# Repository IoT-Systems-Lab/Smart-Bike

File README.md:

# Smart Bike Project group A

This repository contains the work for our **Smart Bike** project, part of the university IoT lab.  
The goal is to design a lightweight, low-power system that collects and transmits sensor data from a bicycle in real time — the first step toward a fully autonomous bike.

---

## Project Overview

The Smart Bike is equipped with several sensors to monitor movement, position, and environment data.  
All information is sent wirelessly to a gateway, which forwards it to a dashboard for live visualization.

We aim to:
- Collect data from multiple onboard sensors (speed, IMU, GPS, environment, …)
- Transmit it using **BLE 5 Long Range** to a **low-power gateway**
- Forward the processed data to a **dashboard** via **Wi-Fi**
- Keep everything lightweight, efficient, and modular

---

## System Architecture

**1. Bike (Sensor Node)**  
- Equipped with sensors for motion, speed, and environment  
- Communicates via **Bluetooth Low Energy (BLE 5 LR)**  

**2. Gateway**  
- Based on **ESP32-C3** microcontroller  
- Receives BLE data and sends it to the dashboard over Wi-Fi  
- Optimized for low power and simple integration  

**3. Dashboard**  
- Displays live bike data  
- Can be web-based or desktop-based  

---

## Group A Members

| Name               | Team                 | Role                   |
|--------------------|----------------------|------------------------|
| Beau Forrez        | Gateway & Dashboard  |                        |
| Elias Neels        | Gateway & Dashboard  |                        |
| Kjell Naessens     | Gateway & Dashboard  | Team Leader            |
| Wout Batselé       | Gateway & Dashboard  |                        |
| Charlotte Bert     | Sensors              | Time manager           |
| Niels Verhoeve     | Sensors              | Communication manager  |
| Arne Van der Stede | Sensors              |                        |
| Syme Vandenbosch   | Sensors              | Buget manager          |
| Daan Vercammen     | Sensors              | Team Leader            |

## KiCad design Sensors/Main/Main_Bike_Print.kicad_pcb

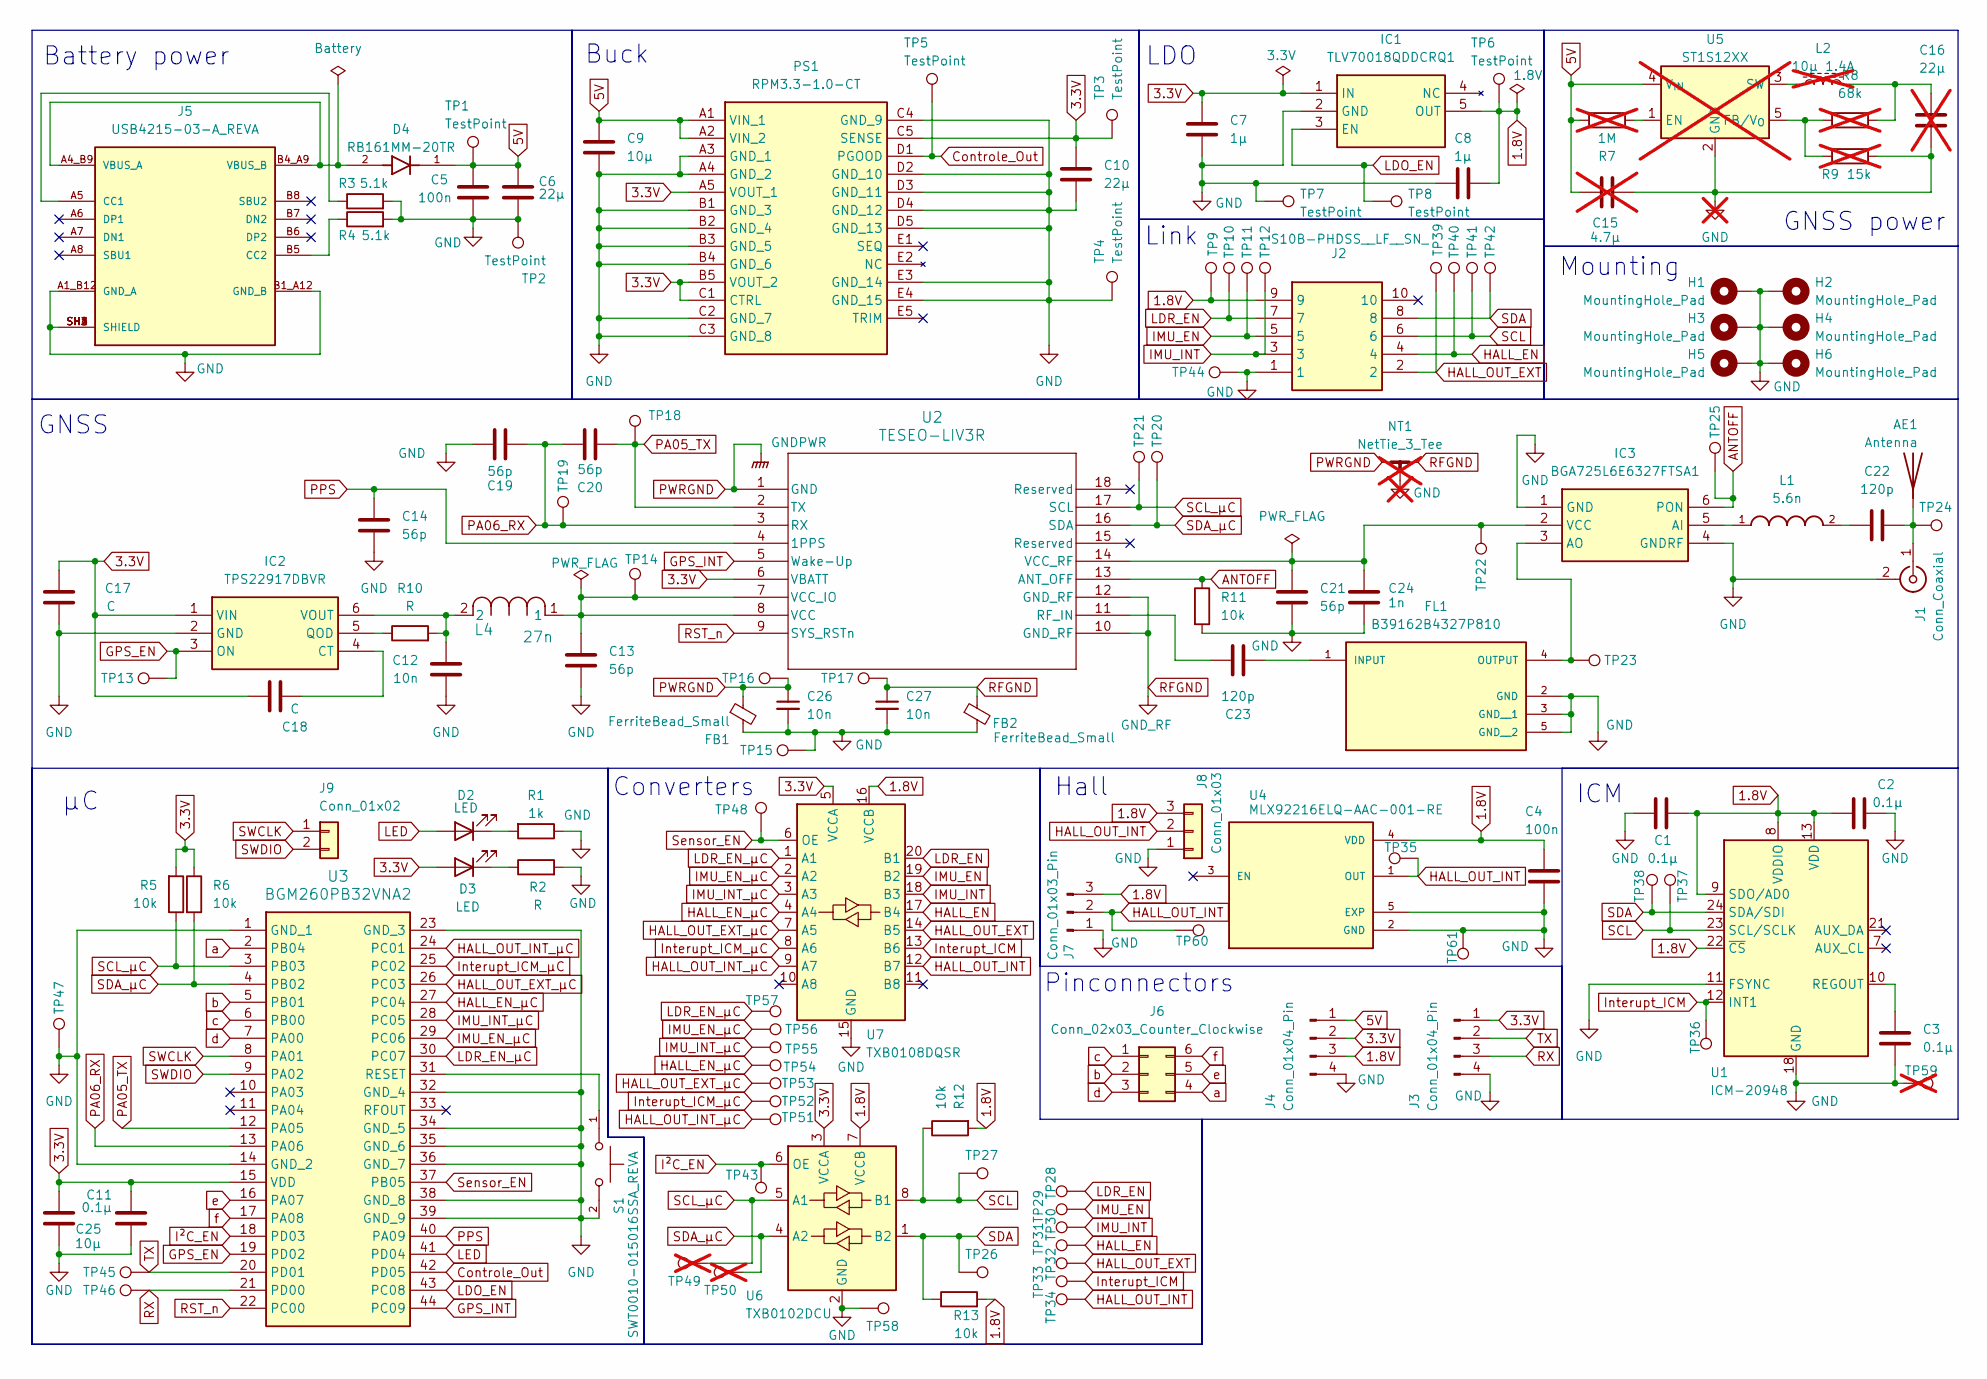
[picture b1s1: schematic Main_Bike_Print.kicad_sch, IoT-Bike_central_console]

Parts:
AE1: Antenna
C1, C2, C3, C11: 0.1µ; C_0603_1608Metric_Pad1.08x0.95mm_HandSolder
C4, C5: 100n; C_0603_1608Metric_Pad1.08x0.95mm_HandSolder
C6, C10: 22µ; C_0603_1608Metric_Pad1.08x0.95mm_HandSolder
C7, C8: 1µ; C_0603_1608Metric_Pad1.08x0.95mm_HandSolder
C9, C25: 10µ; C_0603_1608Metric_Pad1.08x0.95mm_HandSolder
C12, C26, C27: 10n; C_0603_1608Metric_Pad1.08x0.95mm_HandSolder
C13, C14, C19, C20, C21: 56p; C_0603_1608Metric_Pad1.08x0.95mm_HandSolder
C15: 4.7µ; not fitted
C16: 22µ; not fitted
C17, C18: C; C_0603_1608Metric_Pad1.08x0.95mm_HandSolder
C22, C23: 120p; C_0603_1608Metric_Pad1.08x0.95mm_HandSolder
C24: 1n; C_0603_1608Metric_Pad1.08x0.95mm_HandSolder
D2, D3: LED; LED_0603_1608Metric_Pad1.05x0.95mm_HandSolder
D4: RB161MM-20TR; RB161MM20TR
FB1, FB2: FerriteBead_Small; L_0603_1608Metric_Pad1.05x0.95mm_HandSolder
FL1: B39162B4327P810; FIL_B39162B4327P810; PARTREV October 25, 2019
H1, H2, H3, H4, H5, H6: MountingHole_Pad; MountingHole_3.2mm_M3_Pad_Via
IC1: TLV70018QDDCRQ1; SOT95P280X110-5N; Mouser Part Number 595-TLV70018QDDCRQ1
IC2: TPS22917DBVR; SOT95P280X145-6N; Mouser Part Number 595-TPS22917DBVR
IC3: BGA725L6E6327FTSA1; BGS12SN6E6327XTSA1; Manufacturer_Part_Number BGA725L6E6327FTSA1
J1: Conn_Coaxial; U.FL_Hirose_U.FL-R-SMT-1_Vertical
J2: S10B-PHDSS__LF__SN_; S10BPHDSSLFSN; Manufacturer_Part_Number S10B-PHDSS (LF)(SN)
J3, J4: Conn_01x04_Pin; PinSocket_1x04_P2.54mm_Vertical
J5: USB4215-03-A_REVA; GCT_USB4215-03-A_REVA; PARTREV A
J6: Conn_02x03_Counter_Clockwise; PinHeader_2x03_P2.54mm_Vertical
J7: Conn_01x03_Pin; PinSocket_1x03_P2.54mm_Vertical
J8: Conn_01x03; JST_PH_S3B-PH-K_1x03_P2.00mm_Horizontal
J9: Conn_01x02; PinSocket_1x02_P2.54mm_Vertical
L1: 5.6n; IND_0402CS-5N6XJRW; PARTREV 08/06/21
L2: 10µ 1.4A; not fitted
L4: 27n; IND_LQG15HNR10J02_MUR
NT1: NetTie_3_Tee; NetTie-3_SMD_Pad2.0mm; not fitted
PS1: RPM3.3-1.0-CT; RPM3310CT; Manufacturer_Part_Number RPM3.3-1.0-CT
R1: 1k; R_0603_1608Metric_Pad0.98x0.95mm_HandSolder
R2, R10: R; R_0603_1608Metric_Pad0.98x0.95mm_HandSolder
R3, R4: 5.1k; R_0603_1608Metric_Pad0.98x0.95mm_HandSolder
R5, R6, R11, R12, R13: 10k; R_0603_1608Metric_Pad0.98x0.95mm_HandSolder
R7: 1M; not fitted
R8: 68k; not fitted
R9: 15k; not fitted
S1: SWT0010-015016SSA_REVA; SW_SWT0010-015016SSA_REVA; PARTREV A
TP1, TP2, TP3, TP4, TP5, TP6, TP7, TP8, TP9, TP10, TP11, TP12, TP13, TP14, TP15, TP16, TP17, TP18, TP19, TP20, TP21, TP22, TP23, TP24, TP25, TP26, TP27, TP28, TP29, TP30, TP31, TP32, TP33, TP34, TP35, TP36, TP37, TP38, TP39, TP40, TP41, TP42, TP43, TP44, TP45, TP46, TP47, TP48, TP51, TP52, TP53, TP54, TP55, TP56, TP57, TP58, TP60, TP61: TestPoint; TestPoint_Pad_D1.0mm
TP49, TP50, TP59: TestPoint; TestPoint_Pad_D1.0mm; not fitted
U1: ICM-20948; InvenSense_QFN-24_3x3mm_P0.4mm
U2: TESEO-LIV3R; ARRAY_LIV3R_STM
U3: BGM260PB32VNA2; Manufacturer_Part_Number BGM260PB32VNA2
U4: MLX92216ELQ-AAC-001-RE; SON65P120X160X40-5N; PARTREV 1.0
U5: ST1S12XX; TSOT-23-5; not fitted
U6: TXB0102DCU; VSSOP-8_2.3x2mm_P0.5mm
U7: TXB0108DQSR; USON-20_2x4mm_P0.4mm

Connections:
1.8V: C1.2, C2.1, C4.1, C8.1, IC1.5 (OUT), J2.9, J4.3, J7.3, J8.3, R12.2, R13.2, TP6.1, TP9.1, U1.8 (VDDIO), U1.9 (SDO/AD0), U1.13 (VDD), U1.22 (~CS), U4.4 (VDD), U6.7 (VCCB), U7.16 (VCCB)
3.3V: C7.1, C10.1, C11.2, C17.1, C18.1, C25.2, D3.2 (A), IC1.1 (IN), IC2.1 (VIN), J3.1, J4.2, PS1.A5 (VOUT_1), PS1.B5 (VOUT_2), PS1.C1 (CTRL), PS1.C5 (SENSE), R5.2, R6.1, TP3.1, U2.6 (VBATT), U3.15 (VDD), U6.3 (VCCA), U7.5 (VCCA)
5V: C5.1, C6.1, C9.1, C15.1, D4.1, J4.1, PS1.A1 (VIN_1), PS1.A2 (VIN_2), R7.1, TP1.1, U5.4 (V_{IN})
ANTOFF: IC3.6 (PON), R11.1, TP25.1, U2.13 (ANT_OFF)
Controle_Out: PS1.D1 (PGOOD), TP5.1, U3.42 (PD05)
GND: C1.1, C2.2, C3.2, C4.2, C5.2, C6.2, C7.2, C8.2, C9.2, C10.2, C11.1, C12.2, C13.2, C14.2, C15.2, C16.2, C17.2, C19.2, C21.2, C24.2, C25.1, C26.2, C27.2, FB1.2, FB2.2, FL1.2 (GND), FL1.3 (GND__1), FL1.5 (GND__2), H1.1, H2.1, H3.1, H4.1, H5.1, H6.1, IC1.2 (GND), IC2.2 (GND), IC3.1 (GND), IC3.4 (GNDRF), J1.2 (Ext), J2.1, J3.4, J4.4, J5.A1_B12 (GND_A), J5.B1_A12 (GND_B), J5.SH1 (SHIELD), J5.SH2 (SHIELD), J5.SH3 (SHIELD), J5.SH4 (SHIELD), J7.1, J8.1, NT1.3, PS1.A3 (GND_1), PS1.A4 (GND_2), PS1.B1 (GND_3), PS1.B2 (GND_4), PS1.B3 (GND_5), PS1.B4 (GND_6), PS1.C2 (GND_7), PS1.C3 (GND_8), PS1.C4 (GND_9), PS1.D2 (GND_10), PS1.D3 (GND_11), PS1.D4 (GND_12), PS1.D5 (GND_13), PS1.E3 (GND_14), PS1.E4 (GND_15), R1.1, R2.2, R3.2, R4.2, R9.2, R11.2, S1.2, TP2.1, TP4.1, TP7.1, TP15.1, TP44.1, TP47.1, TP58.1, TP59.1, TP61.1, U1.11 (FSYNC), U1.18 (GND), U1.20 (GND), U3.1 (GND_1), U3.14 (GND_2), U3.23 (GND_3), U3.32 (GND_4), U3.34 (GND_5), U3.35 (GND_6), U3.36 (GND_7), U3.38 (GND_8), U3.39 (GND_9), U4.2 (GND), U4.5 (EXP), U5.2 (GND), U6.2 (GND), U7.15 (GND)
GPS_EN: IC2.3 (ON), TP13.1, U3.19 (PD02)
GPS_INT: U2.5 (Wake-Up), U3.44 (PC09)
HALL_EN: J2.4, TP31.1, TP40.1, U7.17 (B4)
HALL_EN_µC: TP54.1, U3.27 (PC04), U7.4 (A4)
HALL_OUT_EXT: J2.2, TP32.1, TP39.1, U7.14 (B5)
HALL_OUT_EXT_µC: TP53.1, U3.26 (PC03), U7.7 (A5)
HALL_OUT_INT: J7.2, J8.2, TP34.1, TP35.1, TP60.1, U4.1 (OUT), U7.12 (B7)
HALL_OUT_INT_µC: TP51.1, U3.24 (PC01), U7.9 (A7)
IMU_EN: J2.5, TP11.1, TP29.1, U7.19 (B2)
IMU_EN_µC: TP56.1, U3.29 (PC06), U7.2 (A2)
IMU_INT: J2.3, TP12.1, TP30.1, U7.18 (B3)
IMU_INT_µC: TP55.1, U3.28 (PC05), U7.3 (A3)
Interupt_ICM: TP33.1, TP36.1, U1.12 (INT1), U7.13 (B6)
Interupt_ICM_µC: TP52.1, U3.25 (PC02), U7.8 (A6)
I²C_EN: TP43.1, U3.18 (PD03), U6.6 (OE)
LDO_EN: IC1.3 (EN), TP8.1, U3.43 (PC08)
LDR_EN: J2.7, TP10.1, TP28.1, U7.20 (B1)
LDR_EN_µC: TP57.1, U3.30 (PC07), U7.1 (A1)
LED: D2.2 (A), U3.41 (PD04)
unnamed: AE1.1, C22.1, J1.1 (In), TP24.1
unnamed: C16.1, L2.2, R8.1
unnamed: C22.2, L1.2
unnamed: D2.1 (K), R1.2
unnamed: D3.1 (K), R2.1
unnamed: C23.1, FL1.1 (INPUT)
unnamed: FL1.4 (OUTPUT), IC3.3 (AO), TP23.1
unnamed: C18.2, IC2.4 (CT)
unnamed: IC2.5 (QOD), R10.1
unnamed: C12.1, IC2.6 (VOUT), L4.2, R10.2
unnamed: IC3.5 (AI), L1.1
unnamed: C21.1, C24.1, IC3.2 (VCC), TP22.1, U2.14 (VCC_RF)
unnamed: J5.A5 (CC1), R3.1
unnamed: J5.B5 (CC2), R4.1
unnamed: D4.2, J5.A4_B9 (VBUS_A), J5.B4_A9 (VBUS_B)
unnamed: L2.1, U5.3 (SW)
unnamed: R7.2, U5.1 (EN)
unnamed: R8.2, R9.1, U5.5 (FB/V_{O})
unnamed: C3.1, U1.10 (REGOUT)
unnamed: C23.2, U2.11 (RF_IN)
unnamed: C13.1, L4.1, TP14.1, U2.7 (VCC_IO), U2.8 (VCC)
unnamed: S1.1, U3.31 (RESET)
PA05_TX: C20.1, TP18.1, U2.2 (TX), U3.12 (PA05)
PA06_RX: C19.1, C20.2, TP19.1, U2.3 (RX), U3.13 (PA06)
PPS: C14.1, U2.4 (1PPS), U3.40 (PA09)
PWRGND: C26.1, FB1.1, NT1.1, TP16.1, U2.1 (GND)
RFGND: C27.1, FB2.1, NT1.2, TP17.1, U2.10 (GND_RF), U2.12 (GND_RF)
RST_n: U2.9 (SYS_RSTn), U3.22 (PC00)
RX: J3.3, TP46.1, U3.21 (PD00)
SCL: J2.6, R12.1, TP27.1, TP37.1, TP41.1, U1.23 (SCL/SCLK), U6.8 (B1)
SCL_µC: R5.1, TP21.1, TP49.1, U2.17 (SCL), U3.3 (PB03), U6.5 (A1)
SDA: J2.8, R13.1, TP26.1, TP38.1, TP42.1, U1.24 (SDA/SDI), U6.1 (B2)
SDA_µC: R6.2, TP20.1, TP50.1, U2.16 (SDA), U3.4 (PB02), U6.4 (A2)
SWCLK: J9.1, U3.8 (PA01)
SWDIO: J9.2, U3.9 (PA02)
Sensor_EN: TP48.1, U3.37 (PB05), U7.6 (OE)
TX: J3.2, TP45.1, U3.20 (PD01)
a: J6.4, U3.2 (PB04)
b: J6.2, U3.5 (PB01)
c: J6.1, U3.6 (PB00)
d: J6.3, U3.7 (PA00)
e: J6.5, U3.16 (PA07)
f: J6.6, U3.17 (PA08)

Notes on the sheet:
Battery power
Link
Converters
ICM
LDO
Mounting
Pinconnectors
GNSS
Buck
GNSS power
Hall

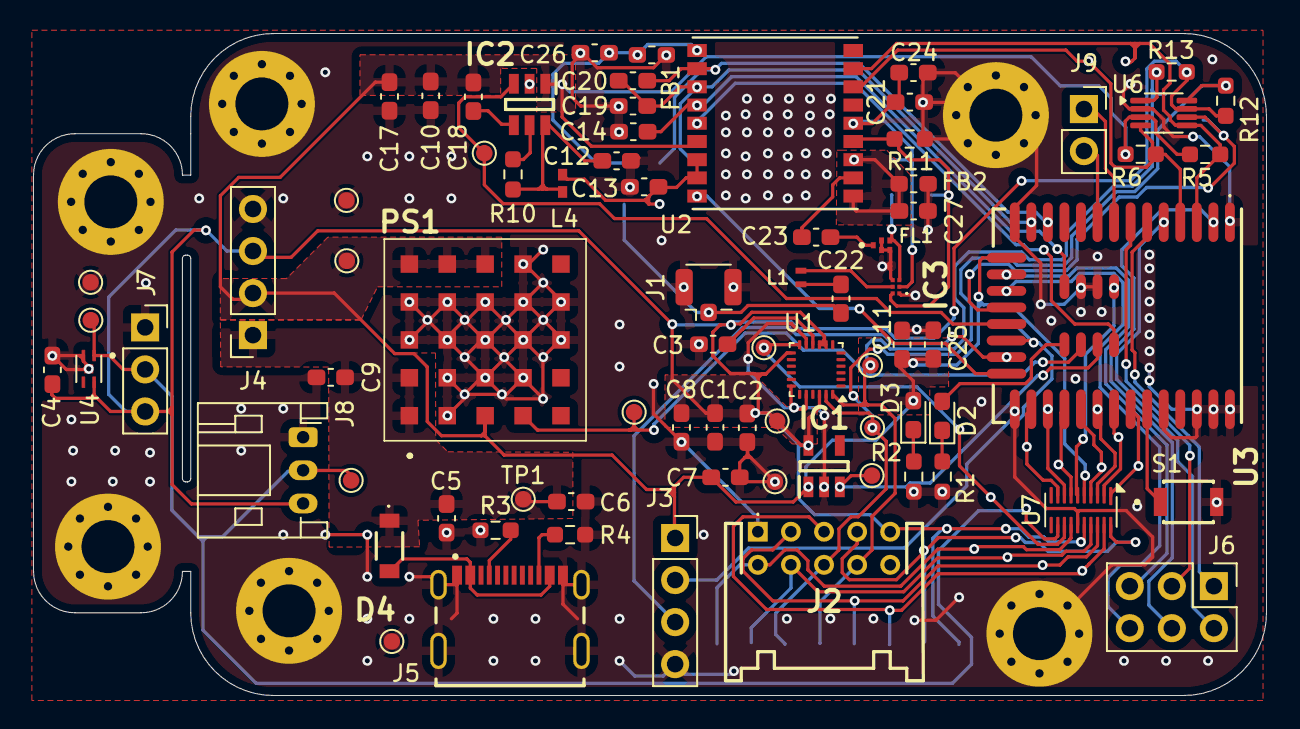
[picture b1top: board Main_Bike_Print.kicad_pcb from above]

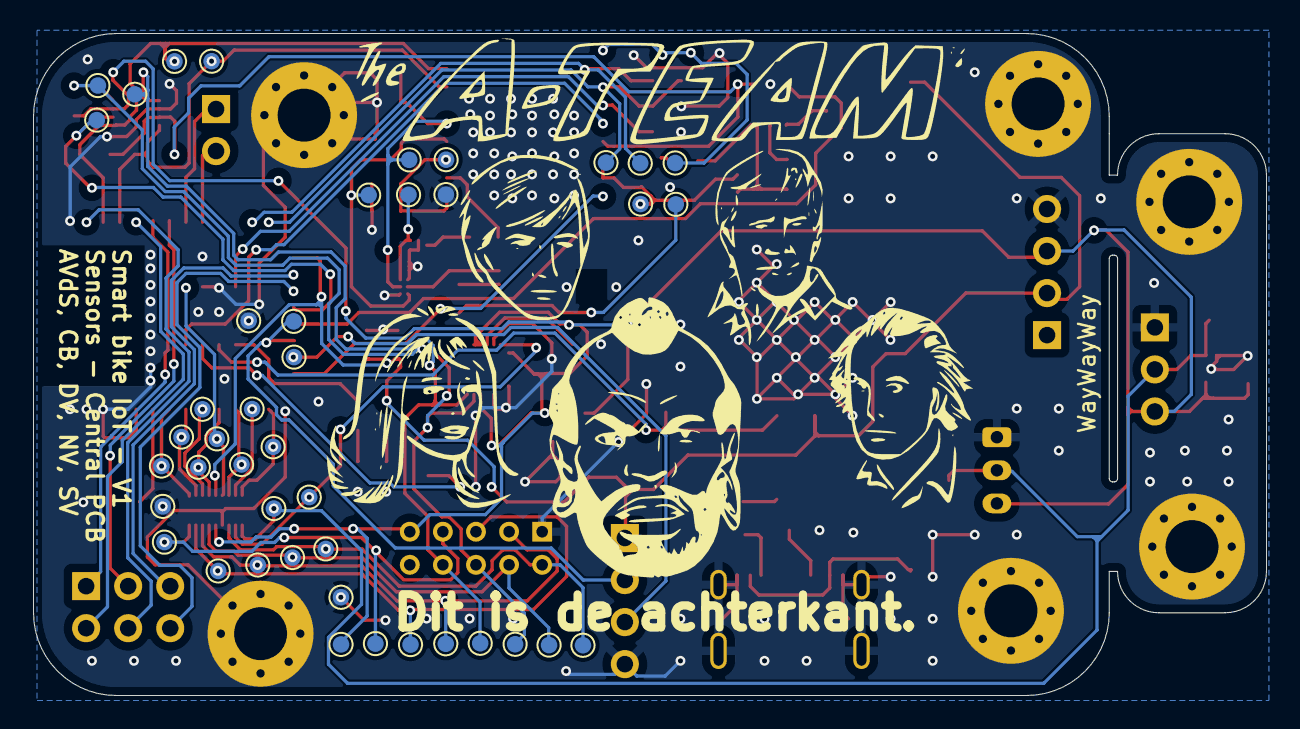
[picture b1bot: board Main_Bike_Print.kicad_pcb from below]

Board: 2 copper layers, 74.5 x 40.0 mm, 127 parts (43 on the bottom side), 64 nets.

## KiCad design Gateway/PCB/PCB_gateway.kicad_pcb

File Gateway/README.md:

# Gateway for Smart Bike Monitoring System

The purpose of the gateway is to receive data from a smart bike over BLE long range and write it to an InfluxDB database over a WiFi connection.
The dashboard is visualized using Grafana. This accesses the InfluxDB database using its HTTP API.

Both the database and the dashboard are hosted in the cloud using free-tier services. The database is hosted on InfluxDB Cloud and the Grafana dashboard is hosted on Grafana Cloud.

It is also possible to host both the database and the dashboard locally using Docker containers. These could be hosted on a personal server. Instructions for these containers are provided in the /Server folder.

## System overview

```
   Smart Bike
         | (BLE long range)
         v
      Gateway
         | (HTTP API)
         v
   InfluxDB Cloud
         | (HTTP API)
         v
   Grafana Cloud
```

## Code for the Gateway

The code for the gateway is written in c++ using the Arduino framework. It is designed to run on an ESP32 microcontroller with both WiFi and BLE long range capabilities.

## Link to dashboard and database

- Gateway WiFi repeater: https://github.com/martin-ger/esp32_nat_router/tree/master
- InfluxDB Cloud: https://cloud2.influxdata.com/
- Grafana Cloud: https://grafana.com/cloud
- Grafana Dashboard: https://boombike.grafana.net/public-dashboards/a31db9c51b8144fbb526a16ae5137e5a?fbclid=IwY2xjawNm6t9leHRuA2FlbQIxMQABHihIpa4uVn0q4TQ20HxuqrC6knFB-QV5GCWbPZI-nRs55s2GTs8DI9WtZkRM_aem_m_eqAt-B783CyasroQSzHg

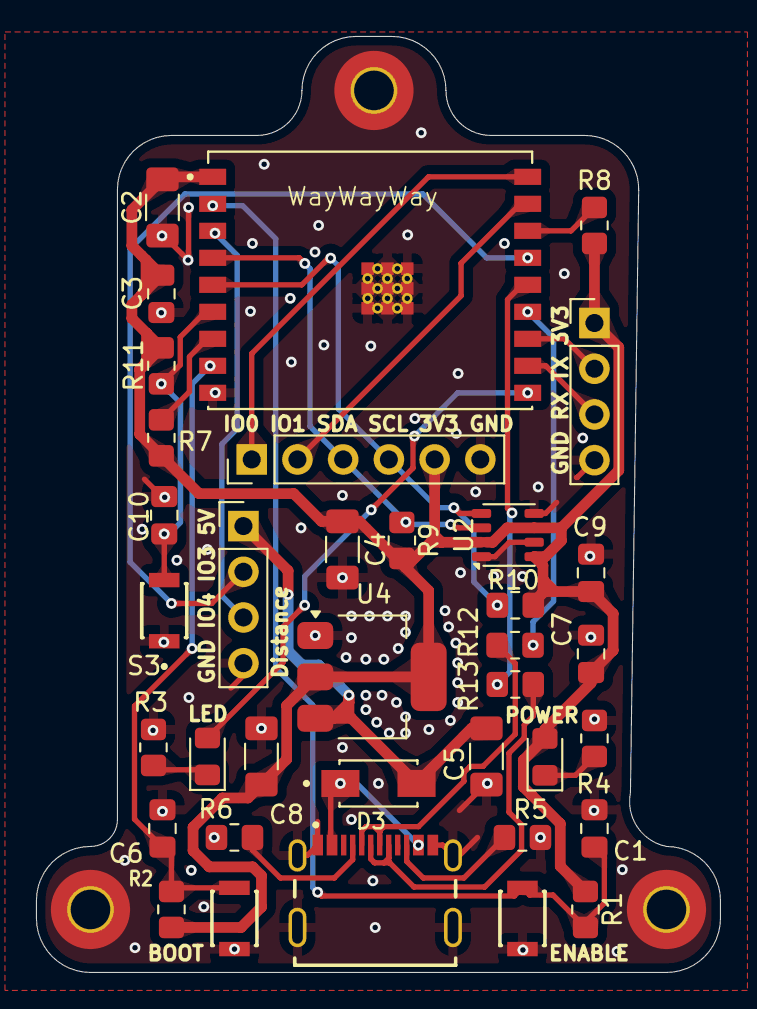
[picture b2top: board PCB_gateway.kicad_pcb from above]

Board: 2 copper layers, 38.0 x 52.0 mm, 39 parts (0 on the bottom side), 26 nets.

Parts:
BOOT: SWT0010-015016SSA_REVA; SW_SWT0010-015016SSA_REVA
C1, C3, C6, C10: 0.1u; C_0805_2012Metric_Pad1.18x1.45mm_HandSolder
C2, C4, C5, C8: 10u; C_1206_3216Metric_Pad1.33x1.80mm_HandSolder
C7, C9: 100n; C_0805_2012Metric_Pad1.18x1.45mm_HandSolder
D3: D_Schottky; DIOM4325X250N
EN: SWT0010-015016SSA_REVA; SW_SWT0010-015016SSA_REVA
H1, H2, H3: MountingHole_Pad; MountingHole_2.2mm_M2_Pad_TopBottom
J1: USB4215-03-A_REVA; GCT_USB4215-03-A_REVA
J2: Conn_01x06_Pin; PinHeader_1x06_P2.54mm_Vertical
J3, J4: Conn_01x04_Pin; PinHeader_1x04_P2.54mm_Vertical
LED: LED; LED_0805_2012Metric_Pad1.15x1.40mm_HandSolder
POWER: LED; LED_0805_2012Metric_Pad1.15x1.40mm_HandSolder
R1, R2, R7, R8, R11: 10k; R_0805_2012Metric_Pad1.20x1.40mm_HandSolder
R3, R4: 1k; R_0805_2012Metric_Pad1.20x1.40mm_HandSolder
R5, R6: 5.1k; R_0805_2012Metric_Pad1.20x1.40mm_HandSolder
R9, R10: 4.7k; R_0805_2012Metric_Pad1.20x1.40mm_HandSolder
R12, R13: 0; R_0805_2012Metric_Pad1.20x1.40mm_HandSolder
S3: SWT0010-015016SSA_REVA; SW_SWT0010-015016SSA_REVA
U1: ESP32-C3-WROOM-02U-N4; XCVR_ESP32-C3-WROOM-02U-N4
U2: BME680; Bosch_LGA-8_3x3mm_P0.8mm_ClockwisePinNumbering
U4: AMS1117-3.3; SOT-223-3_TabPin2

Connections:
+3.3V: C2.2, C3.2, C4.1, C7.1, C8.1, C9.1, J2.5, J3.1, POWER.2 (A), R1.2, R2.2, R7.2, R8.2, R9.1, R10.2, R11.2, U1.1 (3V3), U2.2 (CSB), U2.6 (VDDIO), U2.8 (VDD), U4.2 (VO)
+5V: C5.1, D3.1 (K), J4.1, U4.3 (VI)
BOOT: BOOT.2, C6.2, R2.1, U1.8 (IO9)
D+: R13.1, U1.14 (IO19)
D-: R12.2, U1.13 (IO18)
EN: C1.2, EN.2, R1.1, U1.2 (EN)
GND: BOOT.1, C1.1, C2.1, C3.1, C4.2, C5.2, C6.1, C7.2, C8.2, C9.2, C10.1, EN.1, H1.1, H2.1, H3.1, J1.A1_B12 (GND_A), J1.B1_A12 (GND_B), J1.SH1 (SHIELD), J1.SH2 (SHIELD), J1.SH3 (SHIELD), J1.SH4 (SHIELD), J2.6, J3.4, J4.4, R3.2, R4.2, R5.2, R6.2, S3.1, U1.9 (GND), U1.19_1 (GND), U1.19_2 (GND), U1.19_3 (GND), U1.19_4 (GND), U1.19_5 (GND), U1.19_6 (GND), U1.19_7 (GND), U1.19_8 (GND), U1.19_9 (GND), U1.20_1, U1.20_2, U1.20_3, U1.20_4, U1.20_5, U1.20_6, U1.20_7, U1.20_8, U1.20_9, U1.20_10, U1.20_11, U1.20_12, U2.1 (GND), U2.5 (SDO), U2.7 (GND), U4.1 (GND)
GPIO0: J2.1, U1.18 (IO0)
GPIO1: J2.2, U1.17 (IO1)
GPIO3: J4.2, U1.15 (IO3)
GPIO4: J4.3, U1.3 (IO4)
GPIO7: C10.2, R11.1, S3.2, U1.6 (IO7)
LED: LED.2 (A), U1.10 (IO10)
unnamed: D3.2 (A), J1.A4_B9 (VBUS_A), J1.B4_A9 (VBUS_B)
unnamed: J1.A5 (CC1), R6.1
unnamed: J1.B5 (CC2), R5.1
unnamed: J1.A7 (DN1), J1.B7 (DN2), R12.1
unnamed: J1.A6 (DP1), J1.B6 (DP2), R13.2
unnamed: LED.1 (K), R3.1
unnamed: POWER.1 (K), R4.1
unnamed: R8.1, U1.16 (IO2)
unnamed: R7.1, U1.7 (IO8)
RX: J3.3, U1.11 (RXD/IO20)
SCL: J2.4, R10.1, U1.5 (IO6), U2.4 (SCK)
SDA: J2.3, R9.2, U1.4 (IO5), U2.3 (SDI)
TX: J3.2, U1.12 (TXD/IO21)

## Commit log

2025-10-11 Initial plan
2025-10-11 created folders gateway
2025-10-12 Create temp
2025-10-12 Update PCB design
    DRC errors opgelost, teardrops toegevoegd, routing optimaliseren, kleine details
2025-10-12 update silkscreen
2025-10-14 Create Folder Structure
2025-10-14 Header silkscreen
    added pin description for each header on the silkscreen
2025-10-16 Server and Gateway Initial Commit
2025-10-16 Migrate to InfluxDB Cloud
    Store data in InfluxDB hosted in the cloud instead of transmitting to local database over MQTT
2025-10-19 Added voorvork schematics and PCB
2025-10-20 added main bike pcb files
2025-10-20 Added bom folder
2025-10-20 added bom files
2025-10-23 Code GPS
    Code GPS module + lib BLE (Kjell)
2025-10-23 Update documentation
2025-10-23 Create dashboard
2025-10-23 GPS test
2025-10-23 BME680 added
2025-11-12 Update README.md
    Added Role description
2025-11-12 Delete Sensors/Code/Temp
    Deleted temporary file
2025-11-13 Dummy BLE CODED node
    transmit dummy data to receive with the gateway
2025-11-13 sensors work
2025-11-13 Update links in README for dashboard and database
2025-11-13 Added sensor code for GNSS
2025-11-13 Working Server-Client Example
2025-11-17 Update README with image and project details
    Added an image to the README and clarified the gateway's purpose.
2025-11-17 Add averaging and pass detection to sensor data loop
    Refactors the main loop to sample sensor data at regular intervals, accumulate values for averaging, and publish averaged results periodically. Adds pass detection using the ultrasonic sensor, record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
2025-11-17 Adjust IAQ calculation scaling factor in sampleIfDue function
2025-11-17 Refactor BoomBikeBLE for BLE client functionality
2025-11-18 Delete Sensors/Voorvork/Temp
    Deletion of temporary file
2025-11-28 BLE sensoren
2025-12-01 Arduino test files for backup solution
2025-12-11 Bluetooth parameter update
2025-12-11 Process the incoming data
2025-12-12 Add files via upload
    Werkende code voor opmeten en versturen van onze sensoren.
2025-12-12 add speed data + better BLE parameters
2025-12-15 Change to unique UUID
2025-12-18 Finale versie van de code van team sensors
